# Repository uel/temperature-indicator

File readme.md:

# Temperature Indicator

A 44 component rugged temperature-indicating PCB using solar power and a supercapacitor. Board is designed to
fit in a durable and cost efficent enclosure (PET bottle prefab) and sized exactly to the solar panel. Powered by
supercapacitor to retain charge during low temperatures.

Front             |  Back
:-------------------------:|:-------------------------:
 |

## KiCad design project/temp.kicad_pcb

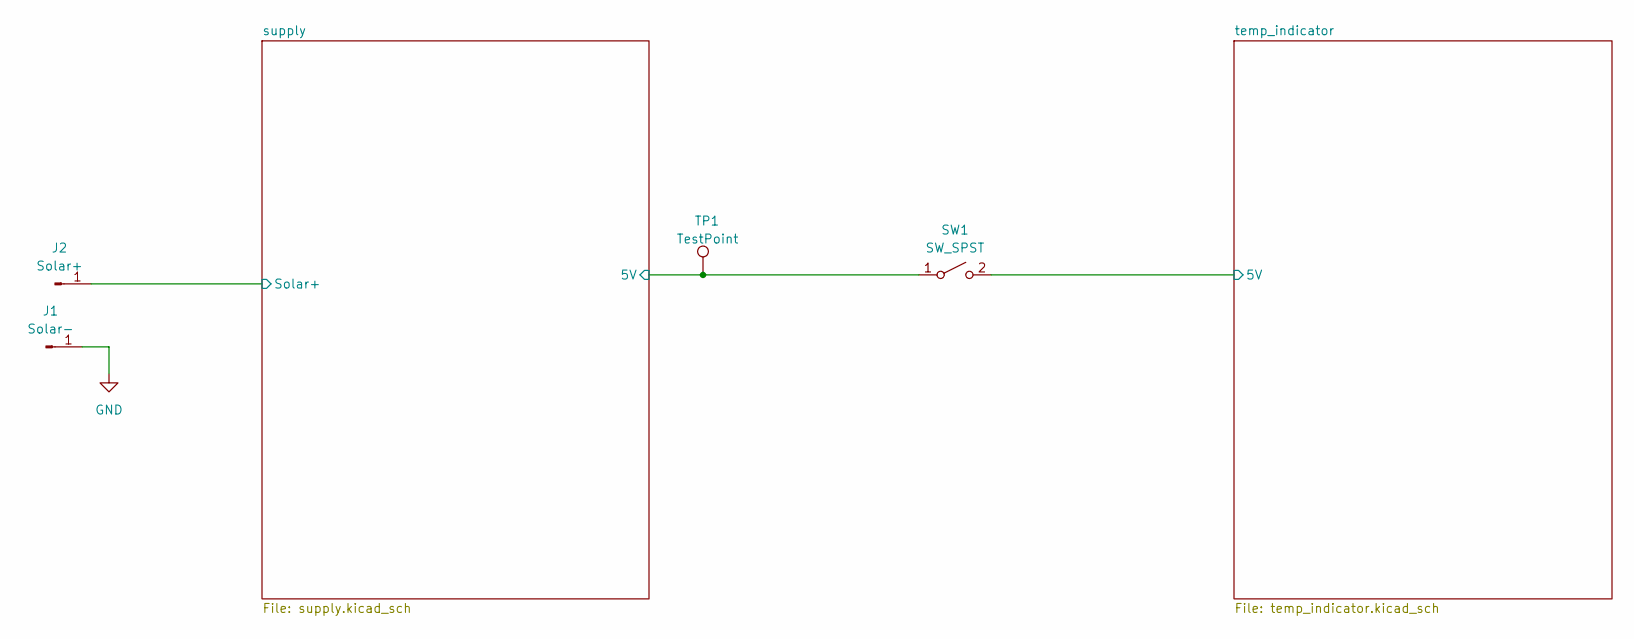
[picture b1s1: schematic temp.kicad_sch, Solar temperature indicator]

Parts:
J1: Solar-; SolderWire-2sqmm_1x01_D2mm_OD3.9mm
J2: Solar+; SolderWire-2sqmm_1x01_D2mm_OD3.9mm
SW1: SW_SPST; C_Radial_D6.3mm_H11.0mm_P2.50mm
TP1: TestPoint; TestPoint_Pad_D2.0mm

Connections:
/supply/5V: SW1.1 (A), TP1.1; also elsewhere on the board
/temp_indicator/5V: SW1.2 (B); also elsewhere on the board

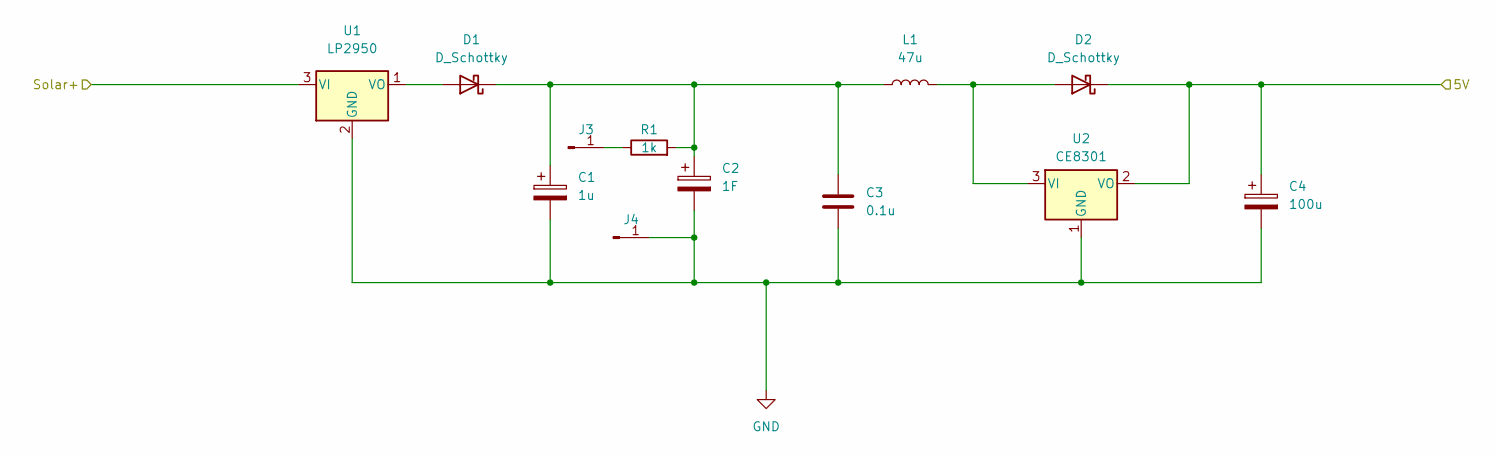
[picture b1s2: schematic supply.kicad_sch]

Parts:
C1: 1u; CP_Radial_D5.0mm_P2.00mm
C2: 1F; CAP_DB-5R5D155T
C3: 0.1u; C_Rect_L7.0mm_W2.0mm_P5.00mm
C4: 100u; CP_Radial_D6.3mm_P2.50mm
D1, D2: D_Schottky; D_DO-35_SOD27_P10.16mm_Horizontal
J3, J4: Conn_01x01_Male; PinHeader_1x01_P2.54mm_Vertical
L1: 47u; L_Axial_L9.5mm_D4.0mm_P12.70mm_Horizontal_Fastron_SMCC
R1: 1k; R_Axial_DIN0207_L6.3mm_D2.5mm_P10.16mm_Horizontal
U1: LP2950; TO-92_Inline
U2: CE8301; SOT-89-3_Handsoldering

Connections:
/supply/5V: C4.1, D2.1 (K), U2.2 (VO); also elsewhere on the board
/supply/Solar+: U1.3 (VI); also elsewhere on the board
GND: C1.2, C2.2, C3.2, C4.2, J4.1, U1.2 (GND), U2.1 (GND); also elsewhere on the board
unnamed: C1.1, C2.1, C3.1, D1.1 (K), L1.1, R1.2
unnamed: D1.2 (A), U1.1 (VO)
unnamed: D2.2 (A), L1.2, U2.3 (VI)
unnamed 27: J3.1, R1.1; also elsewhere on the board

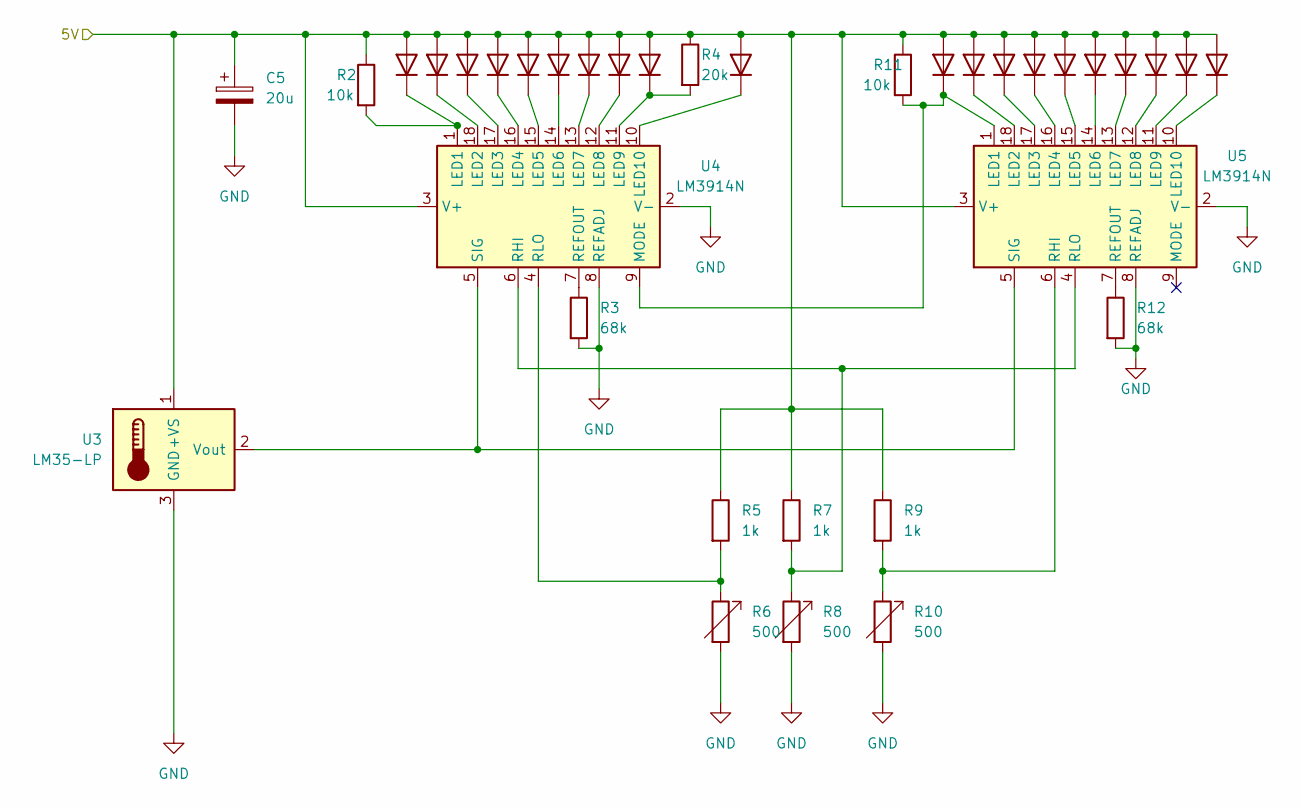
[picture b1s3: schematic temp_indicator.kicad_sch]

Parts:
C5: 20u; CP_Radial_D6.3mm_P2.50mm
D3, D4, D5, D6, D7, D8, D9, D10, D11, D12, D13, D14, D15, D16, D17, D18, D19, D20, D21, D22: D; LED_D3.0mm
R2, R11: 10k; R_Axial_DIN0207_L6.3mm_D2.5mm_P10.16mm_Horizontal
R3, R12: 68k; R_Axial_DIN0207_L6.3mm_D2.5mm_P10.16mm_Horizontal
R4: 20k; R_Axial_DIN0207_L6.3mm_D2.5mm_P10.16mm_Horizontal
R5, R7, R9: 1k; R_Axial_DIN0207_L6.3mm_D2.5mm_P10.16mm_Horizontal
R6, R8, R10: 500; Potentiometer_Piher_PT-6-V_Vertical
U3: LM35-LP; TO-92
U4, U5: LM3914N; DIP-18_W7.62mm

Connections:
/temp_indicator/5V: C5.1, D3.2 (A), D4.2 (A), D5.2 (A), D6.2 (A), D7.2 (A), D8.2 (A), D9.2 (A), D10.2 (A), D11.2 (A), D12.2 (A), D13.2 (A), D14.2 (A), D15.2 (A), D16.2 (A), D17.2 (A), D18.2 (A), D19.2 (A), D20.2 (A), D21.2 (A), D22.2 (A), R2.1, R4.1, R5.1, R7.1, R9.1, R11.1, U3.1 (+VS), U4.3 (V+), U5.3 (V+); also elsewhere on the board
GND: C5.2, R3.2, R6.2, R8.2, R10.2, R12.2, U3.3 (GND), U4.2 (V-), U4.8 (REFADJ), U5.2 (V-), U5.8 (REFADJ); also elsewhere on the board
unnamed: D3.1 (K), R2.2, U4.1 (LED1)
unnamed: D4.1 (K), U4.18 (LED2)
unnamed: D5.1 (K), U4.17 (LED3)
unnamed: D6.1 (K), U4.16 (LED4)
unnamed: D7.1 (K), U4.15 (LED5)
unnamed: D8.1 (K), U4.14 (LED6)
unnamed: D9.1 (K), U4.13 (LED7)
unnamed: D10.1 (K), U4.12 (LED8)
unnamed: D11.1 (K), R4.2, U4.11 (LED9)
unnamed: D12.1 (K), U4.10 (LED10)
unnamed: D13.1 (K), R11.2, U4.9 (MODE), U5.1 (LED1)
unnamed: D14.1 (K), U5.18 (LED2)
unnamed: D15.1 (K), U5.17 (LED3)
unnamed: D16.1 (K), U5.16 (LED4)
unnamed: D17.1 (K), U5.15 (LED5)
unnamed: D18.1 (K), U5.14 (LED6)
unnamed: D19.1 (K), U5.13 (LED7)
unnamed: D20.1 (K), U5.12 (LED8)
unnamed: D21.1 (K), U5.11 (LED9)
unnamed: D22.1 (K), U5.10 (LED10)
unnamed: R3.1, U4.7 (REFOUT)
unnamed: R5.2, R6.1, U4.4 (RLO)
unnamed: R7.2, R8.1, U4.6 (RHI), U5.4 (RLO)
unnamed: R9.2, R10.1, U5.6 (RHI)
unnamed: R12.1, U5.7 (REFOUT)
unnamed: U3.2 (Vout), U4.5 (SIG), U5.5 (SIG)

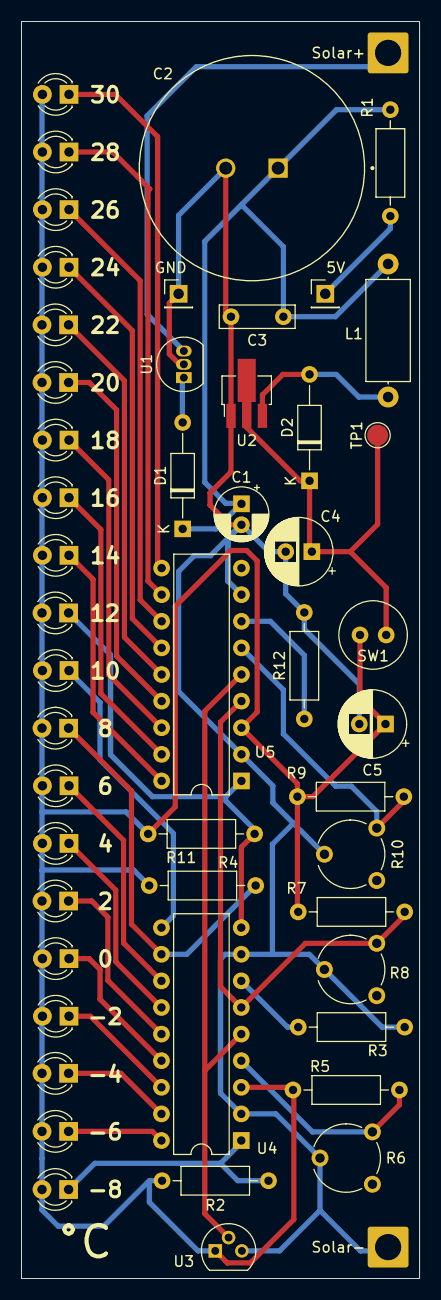
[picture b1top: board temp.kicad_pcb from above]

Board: 2 copper layers, 38.0 x 120.0 mm, 51 parts (0 on the bottom side), 34 nets.

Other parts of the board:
5V: Conn_01x01_Male; PinHeader_1x01_P2.54mm_Vertical
GND: Conn_01x01_Male; PinHeader_1x01_P2.54mm_Vertical
Solar+: Solar+; SolderWire-2sqmm_1x01_D2mm_OD3.9mm
Solar-: Solar-; SolderWire-2sqmm_1x01_D2mm_OD3.9mm

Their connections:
/supply/Solar+: Solar+.1; also elsewhere on the board
GND: GND.1, Solar-.1; also elsewhere on the board
unnamed 27: 5V.1; also elsewhere on the board
